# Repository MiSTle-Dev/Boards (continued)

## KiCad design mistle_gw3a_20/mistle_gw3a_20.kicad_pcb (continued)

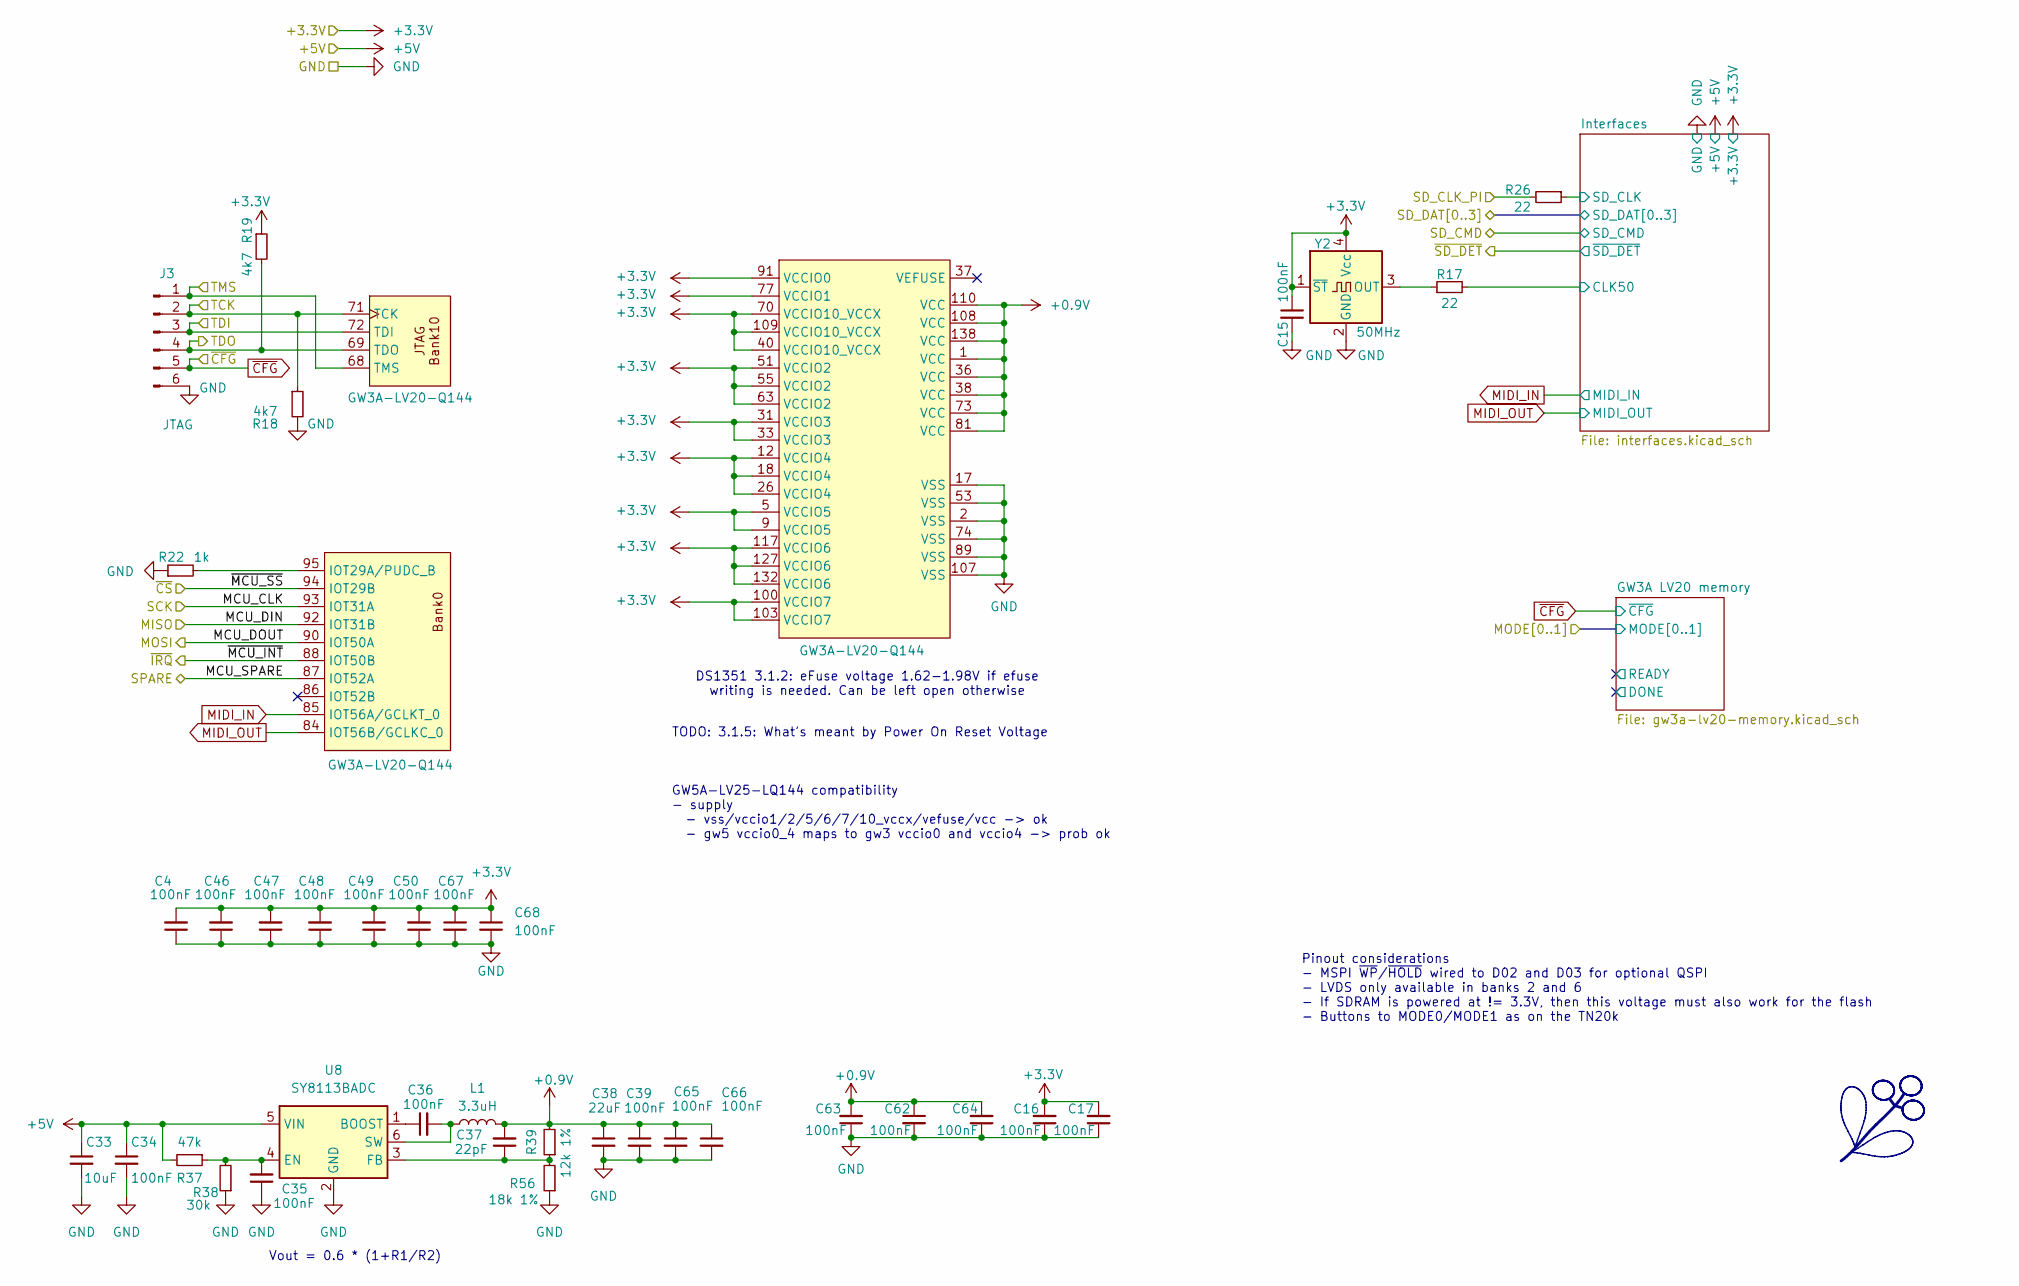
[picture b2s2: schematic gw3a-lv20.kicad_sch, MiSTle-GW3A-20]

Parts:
C4, C15, C16, C17, C35, C36, C46, C47, C48, C49, C50, C62, C63, C64, C65, C66, C67, C68: 100nF; C_0402_1005Metric; LCSC Part # C1525
C33: 10uF; C_0603_1608Metric; LCSC Part # C19702
C34, C39: 100nF; C_0603_1608Metric; LCSC Part # C14663
C37: 22pF; C_0402_1005Metric; LCSC Part # C1555
C38: 22uF; C_0603_1608Metric; LCSC Part # C84419
J3: JTAG; PinHeader_1x06_P2.54mm_Vertical
L1: 3.3uH; L_Sunlord_MWSA0402S; LCSC Part # C408336
R17, R26: 22; R_0402_1005Metric; LCSC Part # C25092
R18, R19: 4k7; R_0402_1005Metric; LCSC Part # C25900
R22: 1k; R_0402_1005Metric; LCSC Part # C11702
R37: 47k; R_0402_1005Metric; LCSC Part # C25792
R38: 30k; R_0402_1005Metric; LCSC Part # C138008
R39: 12k 1%; R_0402_1005Metric; LCSC Part # C25752
R56: 18k 1%; R_0402_1005Metric; LCSC Part # C138044
U7: GW3A-LV20-Q144; LQFP-144_20x20mm_P0.5mm
U8: SY8113BADC; TSOT-23-6; LCSC Part # C78989
Y2: 50MHz; Crystal_SMD_3225-4Pin_3.2x2.5mm; LCSC Part # C2901592

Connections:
+0.9V: C37.2, C38.1, C39.1, C62.1, C63.2, C64.2, C65.1, C66.1, L1.2, R39.2, U7.1 (VCC), U7.36 (VCC), U7.38 (VCC), U7.73 (VCC), U7.81 (VCC), U7.108 (VCC), U7.110 (VCC), U7.138 (VCC)
+3.3V: C4.2, C15.1, C16.2, C17.2, C46.2, C47.2, C48.2, C49.2, C50.2, C67.1, C68.1, R19.1, U7.5 (VCCIO5), U7.9 (VCCIO5), U7.12 (VCCIO4), U7.18 (VCCIO4), U7.26 (VCCIO4), U7.31 (VCCIO3), U7.33 (VCCIO3), U7.40 (VCCIO10_VCCX), U7.51 (VCCIO2), U7.55 (VCCIO2), U7.63 (VCCIO2), U7.70 (VCCIO10_VCCX), U7.77 (VCCIO1), U7.91 (VCCIO0), U7.100 (VCCIO7), U7.103 (VCCIO7), U7.109 (VCCIO10_VCCX), U7.117 (VCCIO6), U7.127 (VCCIO6), U7.132 (VCCIO6), Y2.1 (~ST), Y2.4 (Vcc); also elsewhere on the board
+5V: C33.1, C34.1, R37.2, U8.5 (VIN); also elsewhere on the board
/GW3A-LV20 FPGA/Interfaces/CLK50: R17.2; also elsewhere on the board
/GW3A-LV20 FPGA/Interfaces/SD_CLK: R26.1; also elsewhere on the board
GND: C4.1, C15.2, C16.1, C17.1, C33.2, C34.2, C35.1, C38.2, C39.2, C46.1, C47.1, C48.1, C49.1, C50.1, C62.2, C63.1, C64.1, C65.2, C66.2, C67.2, C68.2, J3.6, R18.2, R22.1, R38.1, R56.1, U7.2 (VSS), U7.17 (VSS), U7.53 (VSS), U7.74 (VSS), U7.89 (VSS), U7.107 (VSS), U8.2 (GND), Y2.2 (GND); also elsewhere on the board
MIDI_IN: U7.85 (IOT56A/GCLKT_0); also elsewhere on the board
MIDI_OUT: U7.84 (IOT56B/GCLKC_0); also elsewhere on the board
MISO: U7.92 (IOT31B); also elsewhere on the board
MOSI: U7.90 (IOT50A); also elsewhere on the board
unnamed: R22.2, U7.95 (IOT29A/PUDC_B)
unnamed: C36.1, U8.1 (BOOST)
unnamed: C35.2, R37.1, R38.2, U8.4 (EN)
unnamed: C37.1, R39.1, R56.2, U8.3 (FB)
unnamed: C36.2, L1.1, U8.6 (SW)
unnamed: R17.1, Y2.3 (OUT)
SCK: U7.93 (IOT31A); also elsewhere on the board
SD_CLK_PI: R26.2; also elsewhere on the board
SPARE: U7.87 (IOT52A); also elsewhere on the board
TCK: J3.2, R18.1, U7.71 (TCK); also elsewhere on the board
TDI: J3.3, U7.72 (TDI); also elsewhere on the board
TDO: J3.4, R19.2, U7.69 (TDO); also elsewhere on the board
TMS: J3.1, U7.68 (TMS); also elsewhere on the board
~CFG: J3.5; also elsewhere on the board
~CS: U7.94 (IOT29B); also elsewhere on the board
~IRQ: U7.88 (IOT50B); also elsewhere on the board

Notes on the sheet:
Vout = 0.6 * (1+R1/R2)
GW5A-LV25-LQ144 compatibility - supply - vss/vccio1/2/5/6/7/10_vccx/vefuse/vcc -> ok - gw5 vccio0_4 maps to gw3 vccio0 and vccio4 -> prob ok
Pinout considerations - MSPI ~{WP}/~{HOLD} wired to D02 and D03 for optional QSPI - LVDS only available in banks 2 and 6 - If SDRAM is powered at != 3.3V, then this voltage must also work for the flash - Buttons to MODE0/MODE1 as on the TN20k
TODO: 3.1.5: What's meant by Power On Reset Voltage
DS1351 3.1.2: eFuse voltage 1.62-1.98V if efuse writing is needed. Can be left open otherwise

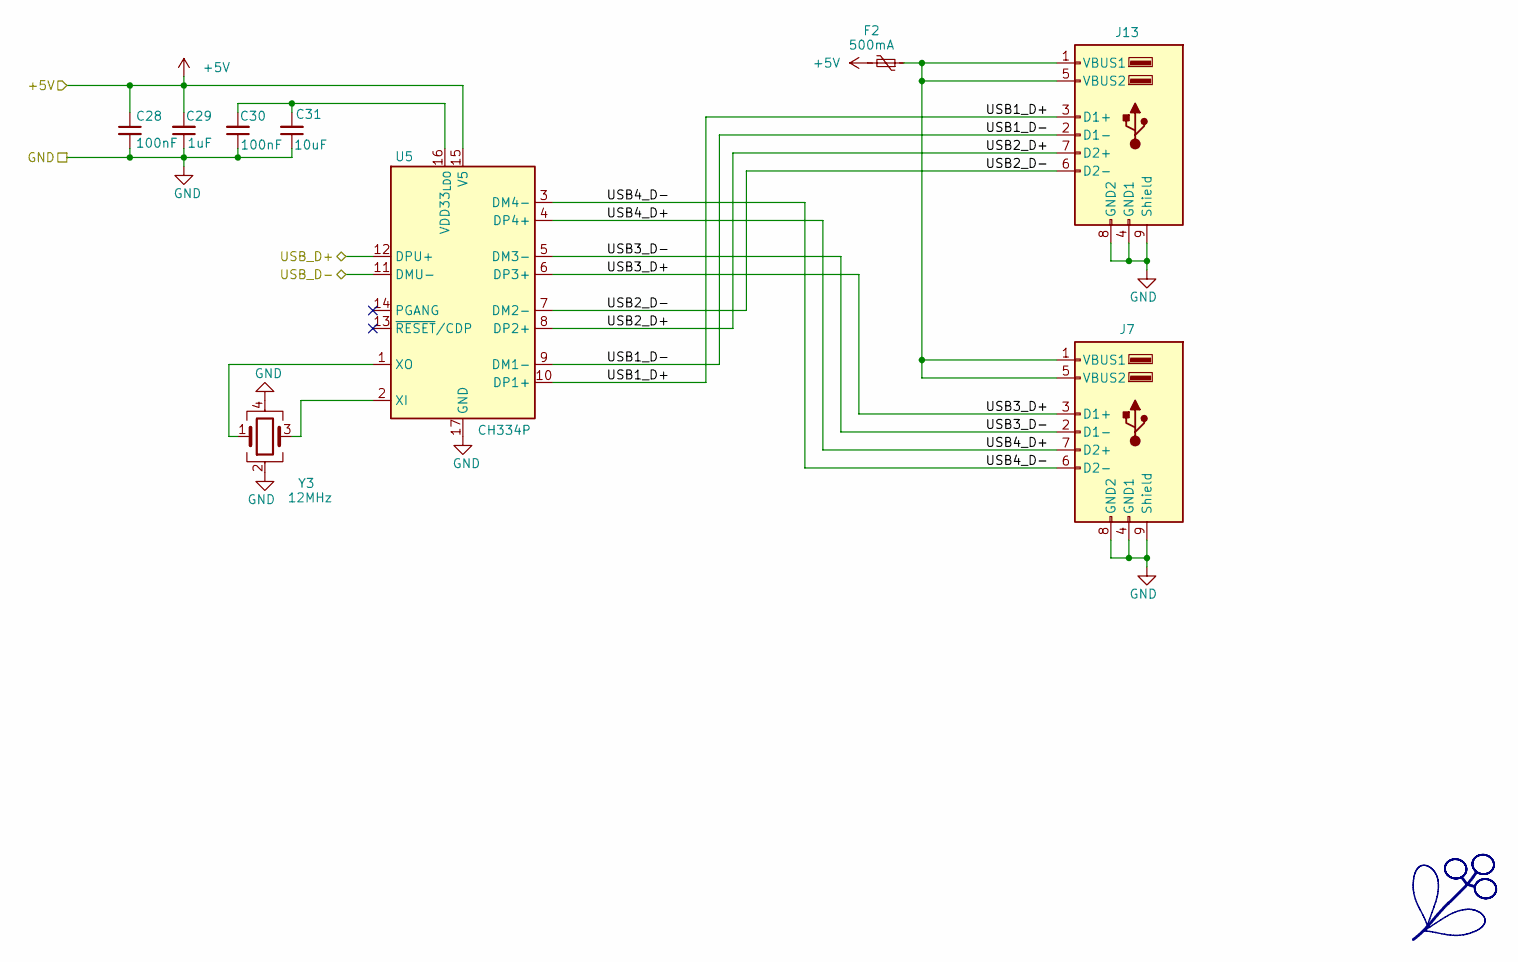
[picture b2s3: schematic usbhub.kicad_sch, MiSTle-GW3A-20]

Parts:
C28, C30: 100nF; C_0402_1005Metric; LCSC Part # C1525
C29: 1uF; C_0402_1005Metric; LCSC Part # C52923
C31: 10uF; C_0402_1005Metric; LCSC Part # C15525
F2: 500mA; Fuse_1206_3216Metric; LCSC Part # C70076
J7, J13: USB_A_Stacked; USB_A_Wuerth_61400826021_Horizontal_Stacked; LCSC Part # C456021
U5: CH334P; QFN-16-1EP_3x3mm_P0.5mm_EP1.45x1.45mm_ThermalVias; LCSC Part # C5373042
Y3: 12MHz; Crystal_SMD_3225-4Pin_3.2x2.5mm; LCSC Part # C9002

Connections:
+5V: C28.1, C29.2, F2.2, U5.15 (V5); also elsewhere on the board
/USB Hub/USB1_D+: J13.3 (D1+), U5.10 (DP1+)
/USB Hub/USB1_D-: J13.2 (D1-), U5.9 (DM1-)
/USB Hub/USB2_D+: J13.7 (D2+), U5.8 (DP2+)
/USB Hub/USB2_D-: J13.6 (D2-), U5.7 (DM2-)
/USB Hub/USB3_D+: J7.3 (D1+), U5.6 (DP3+)
/USB Hub/USB3_D-: J7.2 (D1-), U5.5 (DM3-)
/USB Hub/USB4_D+: J7.7 (D2+), U5.4 (DP4+)
/USB Hub/USB4_D-: J7.6 (D2-), U5.3 (DM4-)
GND: C28.2, C29.1, C30.1, C31.1, J7.4 (GND1), J7.8 (GND2), J7.9 (Shield), J13.4 (GND1), J13.8 (GND2), J13.9 (Shield), U5.17 (GND), Y3.2, Y3.4; also elsewhere on the board
unnamed: F2.1, J7.1 (VBUS1), J7.5 (VBUS2), J13.1 (VBUS1), J13.5 (VBUS2)
unnamed: C30.2, C31.2, U5.16 (VDD33_{LDO})
unnamed: U5.2 (XI), Y3.3
unnamed: U5.1 (XO), Y3.1
USB D+: U5.12 (DPU+); also elsewhere on the board
USB D-: U5.11 (DMU-); also elsewhere on the board

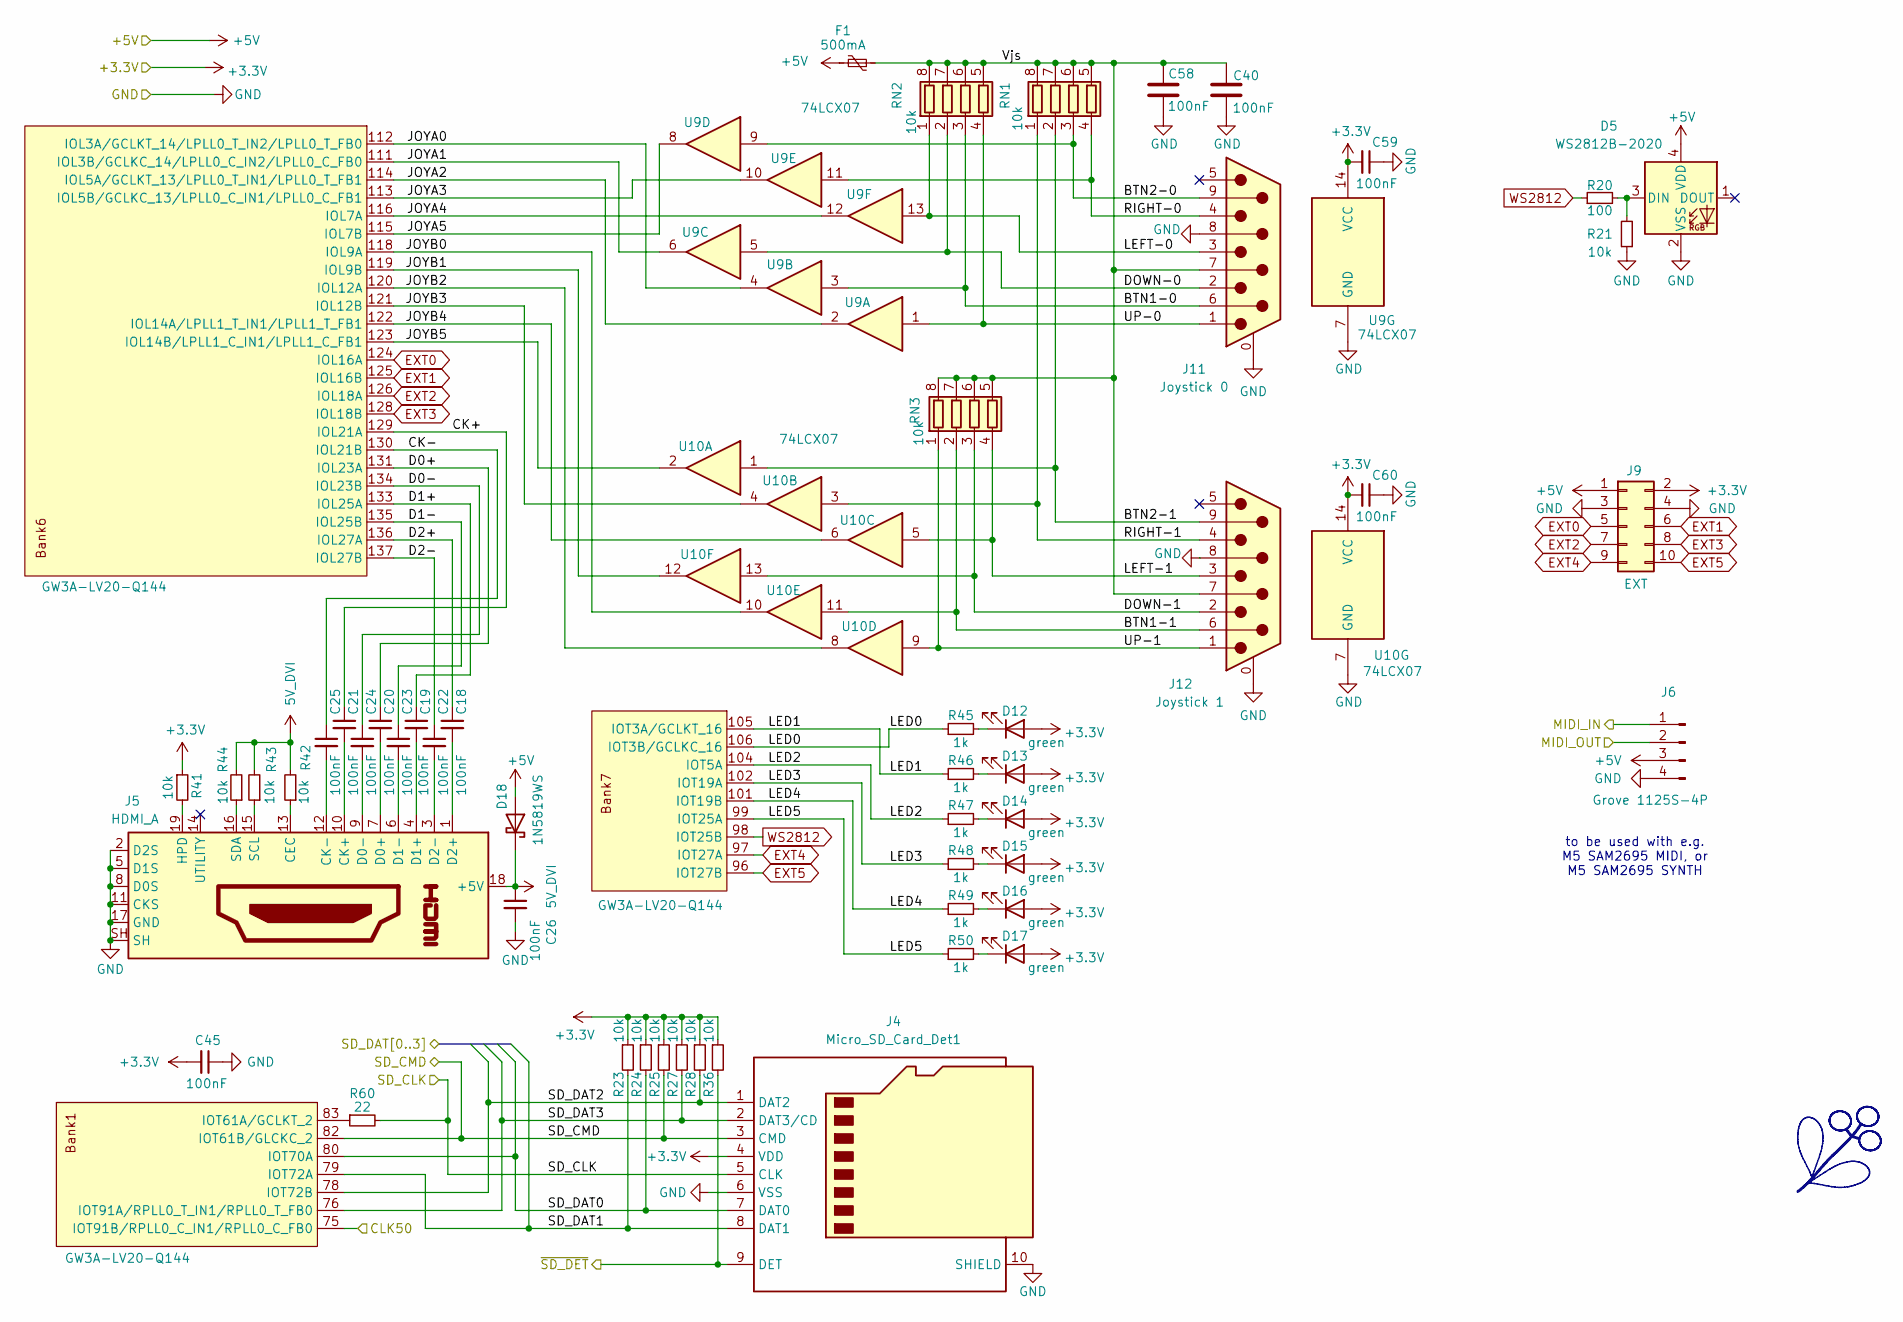
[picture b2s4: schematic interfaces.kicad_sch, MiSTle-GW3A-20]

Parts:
C18, C19, C20, C21, C22, C23, C24, C25, C26, C40, C45, C58, C59, C60: 100nF; C_0402_1005Metric; LCSC Part # C1525
D5: WS2812B-2020; LED_WS2812B-2020_PLCC4_2.0x2.0mm; LCSC Part # C965555
D12, D13, D14, D15, D16, D17: green; LED_0805_2012Metric; LCSC Part # C2297
D18: 1N5819WS; D_SOD-323; LCSC Part # C191023
F1: 500mA; Fuse_1206_3216Metric; LCSC Part # C70076
J4: Micro_SD_Card_Det1; TF-015; LCSC Part # C393941
J5: HDMI_A; HDMI_A_Molex_208658-1001_Horizontal; LCSC Part # C720616
J6: Grove 1125S-4P; NS-Tech_Grove_1x04_P2mm_Vertical
J9: EXT; IDC-Header_2x05_P2.54mm_Vertical; LCSC Part # C271747
J11: Joystick 0; DSUB-9_Pins_Horizontal_P2.77x2.84mm_EdgePinOffset7.70mm_Hou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; LCSC Part # C141880
J12: Joystick 1; DSUB-9_Pins_Horizontal_P2.77x2.84mm_EdgePinOffset7.70mm_Hou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; LCSC Part # C141880
R20: 100; R_0402_1005Metric; LCSC Part # C25076
R21, R23, R24, R25, R27, R28, R36, R41, R42, R43, R44: 10k; R_0402_1005Metric; LCSC Part # C25744
R45, R46, R47, R48, R49, R50: 1k; R_0402_1005Metric; LCSC Part # C11702
R60: 22; R_0402_1005Metric; LCSC Part # C25092
RN1, RN2, RN3: 10k; R_Array_Concave_4x0603; LCSC Part # C110924
U7: GW3A-LV20-Q144; LQFP-144_20x20mm_P0.5mm
U9, U10: 74LCX07; TSSOP-14_4.4x5mm_P0.65mm; LCSC Part # C2676034

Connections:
5V_DVI: C26.1, D18.1 (K), J5.18 (+5V), R42.2, R43.2, R44.2
+3.3V: C45.2, C59.2, C60.2, D12.2 (A), D13.2 (A), D14.2 (A), D15.2 (A), D16.2 (A), D17.2 (A), J4.4 (VDD), J9.2, R23.1, R24.1, R25.1, R27.1, R28.1, R36.1, R41.1, U9.14 (VCC), U10.14 (VCC); also elsewhere on the board
+5V: D5.4 (VDD), D18.2 (A), F1.2, J6.3, J9.1; also elsewhere on the board
/GW3A-LV20 FPGA/Interfaces/BTN1-0: J11.6, RN2.3 (R3.1), U9.3
/GW3A-LV20 FPGA/Interfaces/BTN1-1: J12.6, RN3.2 (R2.1), U10.11
/GW3A-LV20 FPGA/Interfaces/BTN2-0: J11.9, RN1.3 (R3.1), U9.9
/GW3A-LV20 FPGA/Interfaces/BTN2-1: J12.9, RN1.2 (R2.1), U10.1
/GW3A-LV20 FPGA/Interfaces/CK+: C21.1, U7.129 (IOL21A)
/GW3A-LV20 FPGA/Interfaces/CK-: C25.1, U7.130 (IOL21B)
/GW3A-LV20 FPGA/Interfaces/CLK50: U7.75 (IOT91B/RPLL0_C_IN1/RPLL0_C_FB0); also elsewhere on the board
/GW3A-LV20 FPGA/Interfaces/D0+: C20.1, U7.131 (IOL23A)
/GW3A-LV20 FPGA/Interfaces/D0-: C24.1, U7.134 (IOL23B)
/GW3A-LV20 FPGA/Interfaces/D1+: C19.1, U7.133 (IOL25A)
/GW3A-LV20 FPGA/Interfaces/D1-: C23.1, U7.135 (IOL25B)
/GW3A-LV20 FPGA/Interfaces/D2+: C18.1, U7.136 (IOL27A)
/GW3A-LV20 FPGA/Interfaces/D2-: C22.1, U7.137 (IOL27B)
/GW3A-LV20 FPGA/Interfaces/DOWN-0: J11.2, RN2.2 (R2.1), U9.5
/GW3A-LV20 FPGA/Interfaces/DOWN-1: J12.2, RN3.3 (R3.1), U10.13
/GW3A-LV20 FPGA/Interfaces/JOYA0: U7.112 (IOL3A/GCLKT_14/LPLL0_T_IN2/LPLL0_T_FB0), U9.4
/GW3A-LV20 FPGA/Interfaces/JOYA1: U7.111 (IOL3B/GCLKC_14/LPLL0_C_IN2/LPLL0_C_FB0), U9.6
/GW3A-LV20 FPGA/Interfaces/JOYA2: U7.114 (IOL5A/GCLKT_13/LPLL0_T_IN1/LPLL0_T_FB1), U9.2
/GW3A-LV20 FPGA/Interfaces/JOYA3: U7.113 (IOL5B/GCLKC_13/LPLL0_C_IN1/LPLL0_C_FB1), U9.10
/GW3A-LV20 FPGA/Interfaces/JOYA4: U7.116 (IOL7A), U9.12
/GW3A-LV20 FPGA/Interfaces/JOYA5: U7.115 (IOL7B), U9.8
/GW3A-LV20 FPGA/Interfaces/JOYB0: U7.118 (IOL9A), U10.10
/GW3A-LV20 FPGA/Interfaces/JOYB1: U7.119 (IOL9B), U10.12
/GW3A-LV20 FPGA/Interfaces/JOYB2: U7.120 (IOL12A), U10.8
/GW3A-LV20 FPGA/Interfaces/JOYB3: U7.121 (IOL12B), U10.4
/GW3A-LV20 FPGA/Interfaces/JOYB4: U7.122 (IOL14A/LPLL1_T_IN1/LPLL1_T_FB1), U10.6
/GW3A-LV20 FPGA/Interfaces/JOYB5: U7.123 (IOL14B/LPLL1_C_IN1/LPLL1_C_FB1), U10.2
/GW3A-LV20 FPGA/Interfaces/LED0: R45.1, U7.106 (IOT3B/GCLKC_16)
/GW3A-LV20 FPGA/Interfaces/LED1: R46.1, U7.105 (IOT3A/GCLKT_16)
/GW3A-LV20 FPGA/Interfaces/LED2: R47.1, U7.104 (IOT5A)
/GW3A-LV20 FPGA/Interfaces/LED3: R48.1, U7.102 (IOT19A)
/GW3A-LV20 FPGA/Interfaces/LED4: R49.1, U7.101 (IOT19B)
/GW3A-LV20 FPGA/Interfaces/LED5: R50.1, U7.99 (IOT25A)
/GW3A-LV20 FPGA/Interfaces/LEFT-0: J11.3, RN2.1 (R1.1), U9.13
/GW3A-LV20 FPGA/Interfaces/LEFT-1: J12.3, RN3.4 (R4.1), U10.5
/GW3A-LV20 FPGA/Interfaces/RIGHT-0: J11.4, RN1.4 (R4.1), U9.11
/GW3A-LV20 FPGA/Interfaces/RIGHT-1: J12.4, RN1.1 (R1.1), U10.3
/GW3A-LV20 FPGA/Interfaces/SD_CLK: J4.5 (CLK), R60.2; also elsewhere on the board
/GW3A-LV20 FPGA/Interfaces/UP-0: J11.1, RN2.4 (R4.1), U9.1
/GW3A-LV20 FPGA/Interfaces/UP-1: J12.1, RN3.1 (R1.1), U10.9
/GW3A-LV20 FPGA/Interfaces/Vjs: C40.2, C58.2, F1.1, J11.7, J12.7, RN1.5 (R4.2), RN1.6 (R3.2), RN1.7 (R2.2), RN1.8 (R1.2), RN2.5 (R4.2), RN2.6 (R3.2), RN2.7 (R2.2), RN2.8 (R1.2), RN3.5 (R4.2), RN3.6 (R3.2), RN3.7 (R2.2), RN3.8 (R1.2)
EXT0: J9.5, U7.124 (IOL16A)
EXT1: J9.6, U7.125 (IOL16B)
EXT2: J9.7, U7.126 (IOL18A)
EXT3: J9.8, U7.128 (IOL18B)
EXT4: J9.9, U7.97 (IOT27A)
EXT5: J9.10, U7.96 (IOT27B)
GND: C26.2, C40.1, C45.1, C58.1, C59.1, C60.1, D5.2 (VSS), J4.6 (VSS), J4.10 (SHIELD), J5.2 (D2S), J5.5 (D1S), J5.8 (D0S), J5.11 (CKS), J5.17 (GND), J5.SH, J6.4, J9.3, J9.4, J11.0 (PAD), J11.8, J12.0 (PAD), J12.8, R21.1, U9.7 (GND), U10.7 (GND); also elsewhere on the board
MIDI_IN: J6.1; also elsewhere on the board
MIDI_OUT: J6.2; also elsewhere on the board
unnamed: D5.3 (DIN), R20.2, R21.2
unnamed: D12.1 (K), R45.2
unnamed: D13.1 (K), R46.2
unnamed: D14.1 (K), R47.2
unnamed: D15.1 (K), R48.2
unnamed: D16.1 (K), R49.2
unnamed: D17.1 (K), R50.2
unnamed: J5.13 (CEC), R42.1
unnamed: C21.2, J5.10 (CK+)
unnamed: C25.2, J5.12 (CK-)
unnamed: C20.2, J5.7 (D0+)
unnamed: C24.2, J5.9 (D0-)
unnamed: C19.2, J5.4 (D1+)
unnamed: C23.2, J5.6 (D1-)
unnamed: C18.2, J5.1 (D2+)
unnamed: C22.2, J5.3 (D2-)
unnamed: J5.19 (HPD), R41.2
unnamed: J5.15 (SCL), R43.1
unnamed: J5.16 (SDA), R44.1
unnamed: R60.1, U7.83 (IOT61A/GCLKT_2)
SD_CMD: J4.3 (CMD), R25.2, U7.82 (IOT61B/GLCKC_2); also elsewhere on the board
SD_DAT0: J4.7 (DAT0), R24.2, U7.80 (IOT70A); also elsewhere on the board
SD_DAT1: J4.8 (DAT1), R23.2, U7.79 (IOT72A)
SD_DAT2: J4.1 (DAT2), R28.2, U7.78 (IOT72B)
SD_DAT3: J4.2 (DAT3/CD), R27.2, U7.76 (IOT91A/RPLL0_T_IN1/RPLL0_T_FB0); also elsewhere on the board
WS2812: R20.1, U7.98 (IOT25B)
~SD_DET: J4.9 (DET), R36.2; also elsewhere on the board

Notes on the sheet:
to be used with e.g. M5 SAM2695 MIDI, or M5 SAM2695 SYNTH

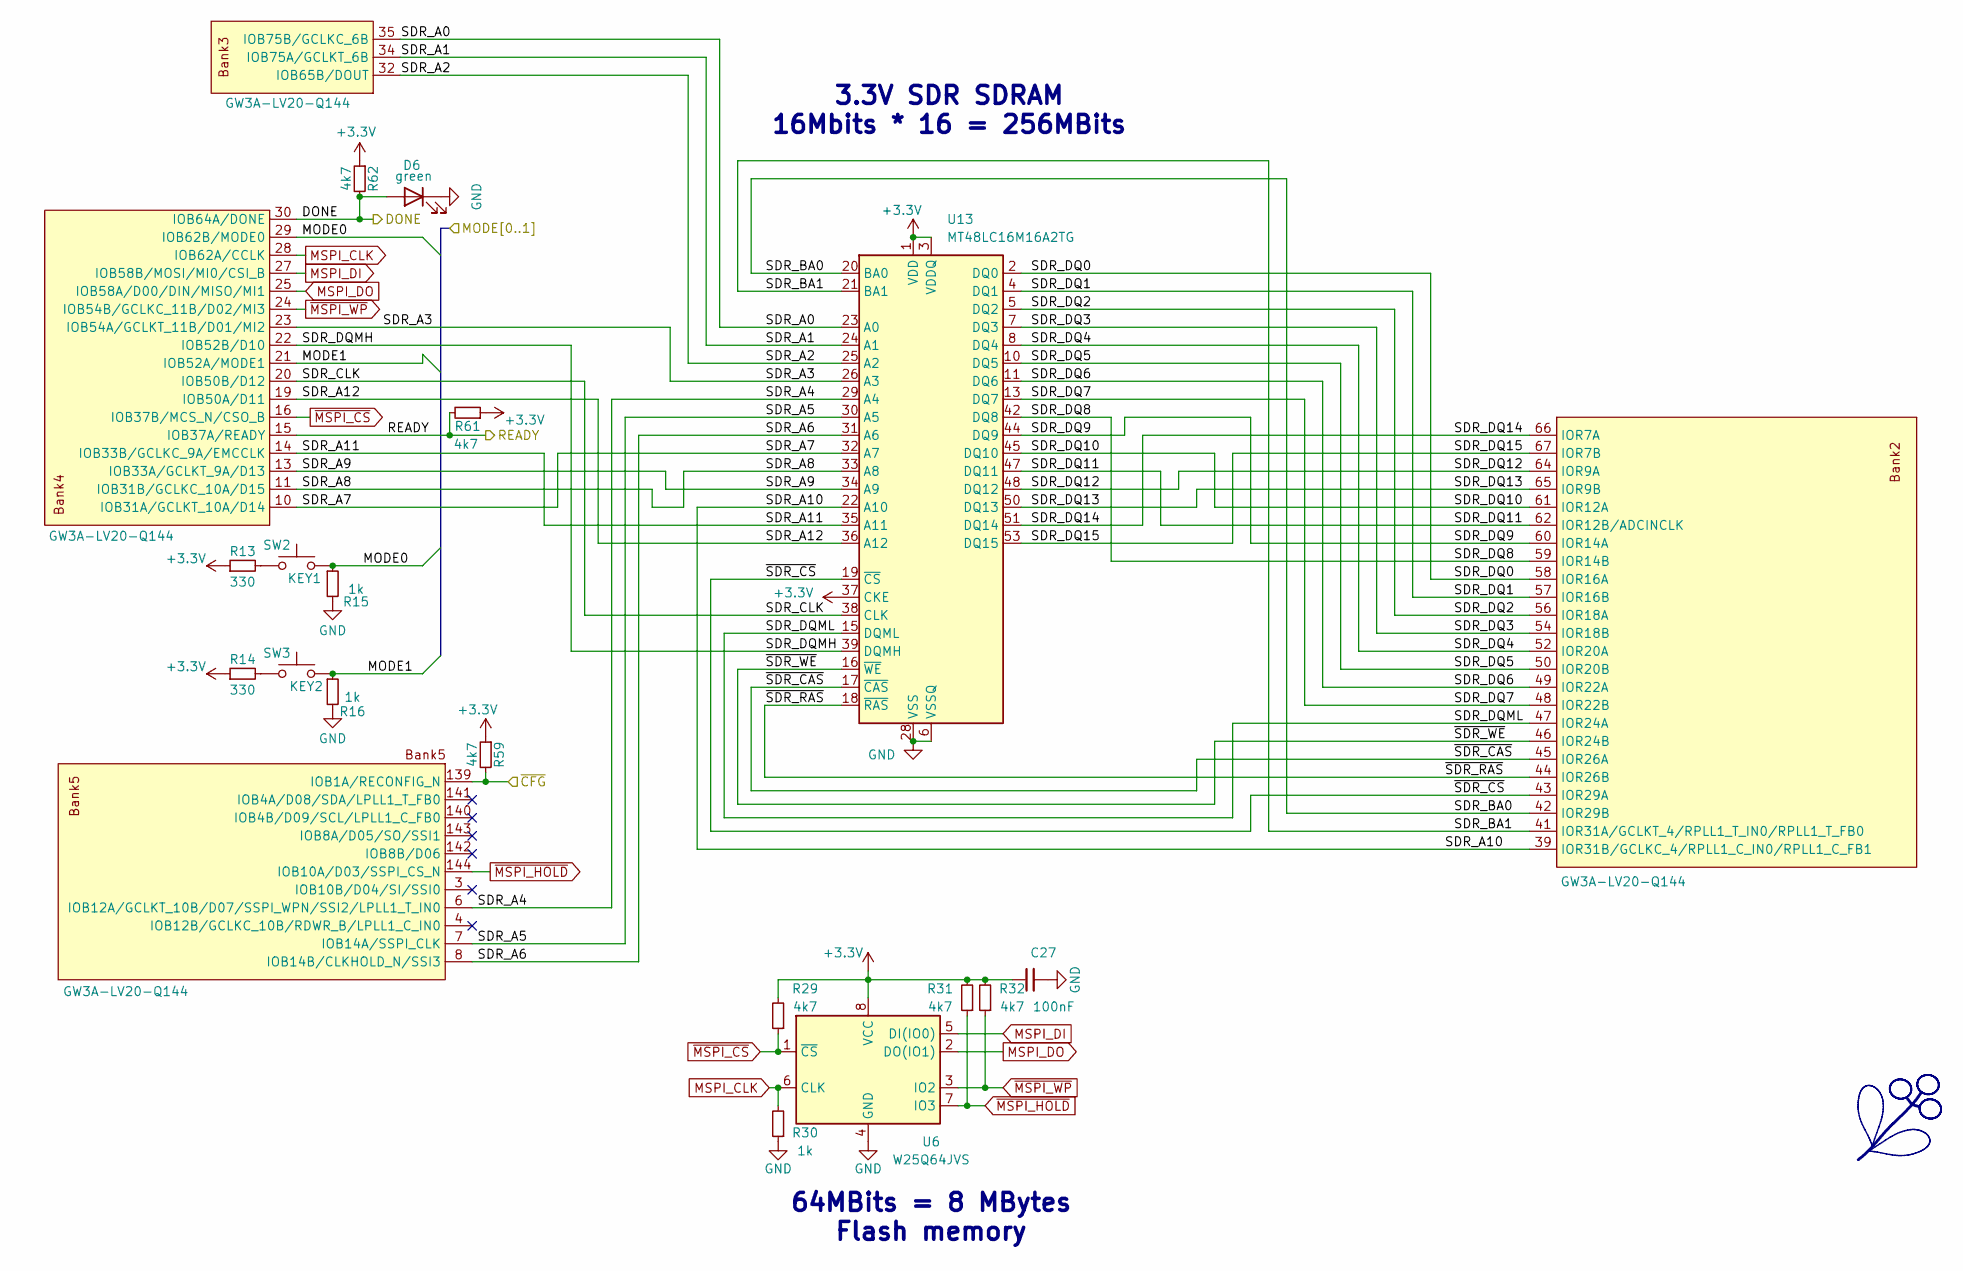
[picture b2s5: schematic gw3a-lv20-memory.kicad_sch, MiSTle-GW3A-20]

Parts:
C27: 100nF; C_0402_1005Metric; LCSC Part # C1525
D6: green; LED_0805_2012Metric; LCSC Part # C2297
R13, R14: 330; R_0402_1005Metric; LCSC Part # C105875
R15, R16, R30: 1k; R_0402_1005Metric; LCSC Part # C11702
R29, R31, R32, R59, R61, R62: 4k7; R_0402_1005Metric; LCSC Part # C25900
SW2: KEY1; SW_SPST_TL3342; LCSC Part # C318884
SW3: KEY2; SW_SPST_TL3342; LCSC Part # C318884
U6: W25Q64JVS; SOIC-8_5.3x5.3mm_P1.27mm; LCSC Part # C179171
U7: GW3A-LV20-Q144; LQFP-144_20x20mm_P0.5mm
U13: MT48LC16M16A2TG; TSOP-II-54_22.2x10.16mm_P0.8mm; LCSC Part # C62246

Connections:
+3.3V: C27.1, R13.1, R14.1, R29.2, R31.2, R32.2, R59.1, R61.1, R62.1, U6.8 (VCC), U13.1 (VDD), U13.3 (VDDQ), U13.9 (VDDQ), U13.14 (VDD), U13.27 (VDD), U13.37 (CKE), U13.43 (VDDQ), U13.49 (VDDQ); also elsewhere on the board
/GW3A-LV20 FPGA/GW3A LV20 memory/DONE: D6.2 (A), R62.2, U7.30 (IOB64A/DONE)
/GW3A-LV20 FPGA/GW3A LV20 memory/READY: R61.2, U7.15 (IOB37A/READY)
/GW3A-LV20 FPGA/GW3A LV20 memory/SDR_A0: U7.35 (IOB75B/GCLKC_6B), U13.23 (A0)
/GW3A-LV20 FPGA/GW3A LV20 memory/SDR_A1: U7.34 (IOB75A/GCLKT_6B), U13.24 (A1)
/GW3A-LV20 FPGA/GW3A LV20 memory/SDR_A2: U7.32 (IOB65B/DOUT), U13.25 (A2)
/GW3A-LV20 FPGA/GW3A LV20 memory/SDR_A3: U7.23 (IOB54A/GCLKT_11B/D01/MI2), U13.26 (A3)
/GW3A-LV20 FPGA/GW3A LV20 memory/SDR_A4: U7.6 (IOB12A/GCLKT_10B/D07/SSPI_WPN/SSI2/LPLL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), U13.29 (A4)
/GW3A-LV20 FPGA/GW3A LV20 memory/SDR_A5: U7.7 (IOB14A/SSPI_CLK), U13.30 (A5)
/GW3A-LV20 FPGA/GW3A LV20 memory/SDR_A6: U7.8 (IOB14B/CLKHOLD_N/SSI3), U13.31 (A6)
/GW3A-LV20 FPGA/GW3A LV20 memory/SDR_A7: U7.10 (IOB31A/GCLKT_10A/D14), U13.32 (A7)
/GW3A-LV20 FPGA/GW3A LV20 memory/SDR_A8: U7.11 (IOB31B/GCLKC_10A/D15), U13.33 (A8)
/GW3A-LV20 FPGA/GW3A LV20 memory/SDR_A9: U7.13 (IOB33A/GCLKT_9A/D13), U13.34 (A9)
/GW3A-LV20 FPGA/GW3A LV20 memory/SDR_A10: U7.39 (IOR31B/GCLKC_4/RPLL1_C_IN0/RPLL1_C_FB1), U13.22 (A10)
/GW3A-LV20 FPGA/GW3A LV20 memory/SDR_A11: U7.14 (IOB33B/GCLKC_9A/EMCCLK), U13.35 (A11)
/GW3A-LV20 FPGA/GW3A LV20 memory/SDR_A12: U7.19 (IOB50A/D11), U13.36 (A12)
/GW3A-LV20 FPGA/GW3A LV20 memory/SDR_BA0: U7.42 (IOR29B), U13.20 (BA0)
/GW3A-LV20 FPGA/GW3A LV20 memory/SDR_BA1: U7.41 (IOR31A/GCLKT_4/RPLL1_T_IN0/RPLL1_T_FB0), U13.21 (BA1)
/GW3A-LV20 FPGA/GW3A LV20 memory/SDR_CLK: U7.20 (IOB50B/D12), U13.38 (CLK)
/GW3A-LV20 FPGA/GW3A LV20 memory/SDR_DQ0: U7.58 (IOR16A), U13.2 (DQ0)
/GW3A-LV20 FPGA/GW3A LV20 memory/SDR_DQ1: U7.57 (IOR16B), U13.4 (DQ1)
/GW3A-LV20 FPGA/GW3A LV20 memory/SDR_DQ2: U7.56 (IOR18A), U13.5 (DQ2)
/GW3A-LV20 FPGA/GW3A LV20 memory/SDR_DQ3: U7.54 (IOR18B), U13.7 (DQ3)
/GW3A-LV20 FPGA/GW3A LV20 memory/SDR_DQ4: U7.52 (IOR20A), U13.8 (DQ4)
/GW3A-LV20 FPGA/GW3A LV20 memory/SDR_DQ5: U7.50 (IOR20B), U13.10 (DQ5)
/GW3A-LV20 FPGA/GW3A LV20 memory/SDR_DQ6: U7.49 (IOR22A), U13.11 (DQ6)
/GW3A-LV20 FPGA/GW3A LV20 memory/SDR_DQ7: U7.48 (IOR22B), U13.13 (DQ7)
/GW3A-LV20 FPGA/GW3A LV20 memory/SDR_DQ8: U7.59 (IOR14B), U13.42 (DQ8)
/GW3A-LV20 FPGA/GW3A LV20 memory/SDR_DQ9: U7.60 (IOR14A), U13.44 (DQ9)
/GW3A-LV20 FPGA/GW3A LV20 memory/SDR_DQ10: U7.61 (IOR12A), U13.45 (DQ10)
/GW3A-LV20 FPGA/GW3A LV20 memory/SDR_DQ11: U7.62 (IOR12B/ADCINCLK), U13.47 (DQ11)
/GW3A-LV20 FPGA/GW3A LV20 memory/SDR_DQ12: U7.64 (IOR9A), U13.48 (DQ12)
/GW3A-LV20 FPGA/GW3A LV20 memory/SDR_DQ13: U7.65 (IOR9B), U13.50 (DQ13)
/GW3A-LV20 FPGA/GW3A LV20 memory/SDR_DQ14: U7.66 (IOR7A), U13.51 (DQ14)
/GW3A-LV20 FPGA/GW3A LV20 memory/SDR_DQ15: U7.67 (IOR7B), U13.53 (DQ15)
/GW3A-LV20 FPGA/GW3A LV20 memory/SDR_DQMH: U7.22 (IOB52B/D10), U13.39 (DQMH)
/GW3A-LV20 FPGA/GW3A LV20 memory/SDR_DQML: U7.47 (IOR24A), U13.15 (DQML)
/GW3A-LV20 FPGA/GW3A LV20 memory/~SDR_CAS: U7.45 (IOR26A), U13.17 (~CAS)
/GW3A-LV20 FPGA/GW3A LV20 memory/~SDR_CS: U7.43 (IOR29A), U13.19 (~CS)
/GW3A-LV20 FPGA/GW3A LV20 memory/~SDR_RAS: U7.44 (IOR26B), U13.18 (~RAS)
/GW3A-LV20 FPGA/GW3A LV20 memory/~SDR_WE: U7.46 (IOR24B), U13.16 (~WE)
GND: C27.2, D6.1 (K), R15.2, R16.2, R30.1, U6.4 (GND), U13.6 (VSSQ), U13.12 (VSSQ), U13.28 (VSS), U13.41 (VSS), U13.46 (VSSQ), U13.52 (VSSQ), U13.54 (VSS); also elsewhere on the board
MODE0: R15.1, SW2.2, U7.29 (IOB62B/MODE0); also elsewhere on the board
MODE1: R16.1, SW3.2, U7.21 (IOB52A/MODE1); also elsewhere on the board
MSPI_CLK: R30.2, U6.6 (CLK), U7.28 (IOB62A/CCLK)
MSPI_DI: U6.5 (DI(IO0)), U7.27 (IOB58B/MOSI/MI0/CSI_B)
MSPI_DO: U6.2 (DO(IO1)), U7.25 (IOB58A/D00/DIN/MISO/MI1)
unnamed: R13.2, SW2.1
unnamed: R14.2, SW3.1
~CFG: R59.2, U7.139 (IOB1A/RECONFIG_N); also elsewhere on the board
~MSPI_CS: R29.1, U6.1 (~CS), U7.16 (IOB37B/MCS_N/CSO_B)
~MSPI_HOLD: R31.1, U6.7 (IO3), U7.144 (IOB10A/D03/SSPI_CS_N)
~MSPI_WP: R32.1, U6.3 (IO2), U7.24 (IOB54B/GCLKC_11B/D02/MI3)

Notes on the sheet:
64MBits = 8 MBytes Flash memory
3.3V SDR SDRAM 16Mbits * 16 = 256MBits

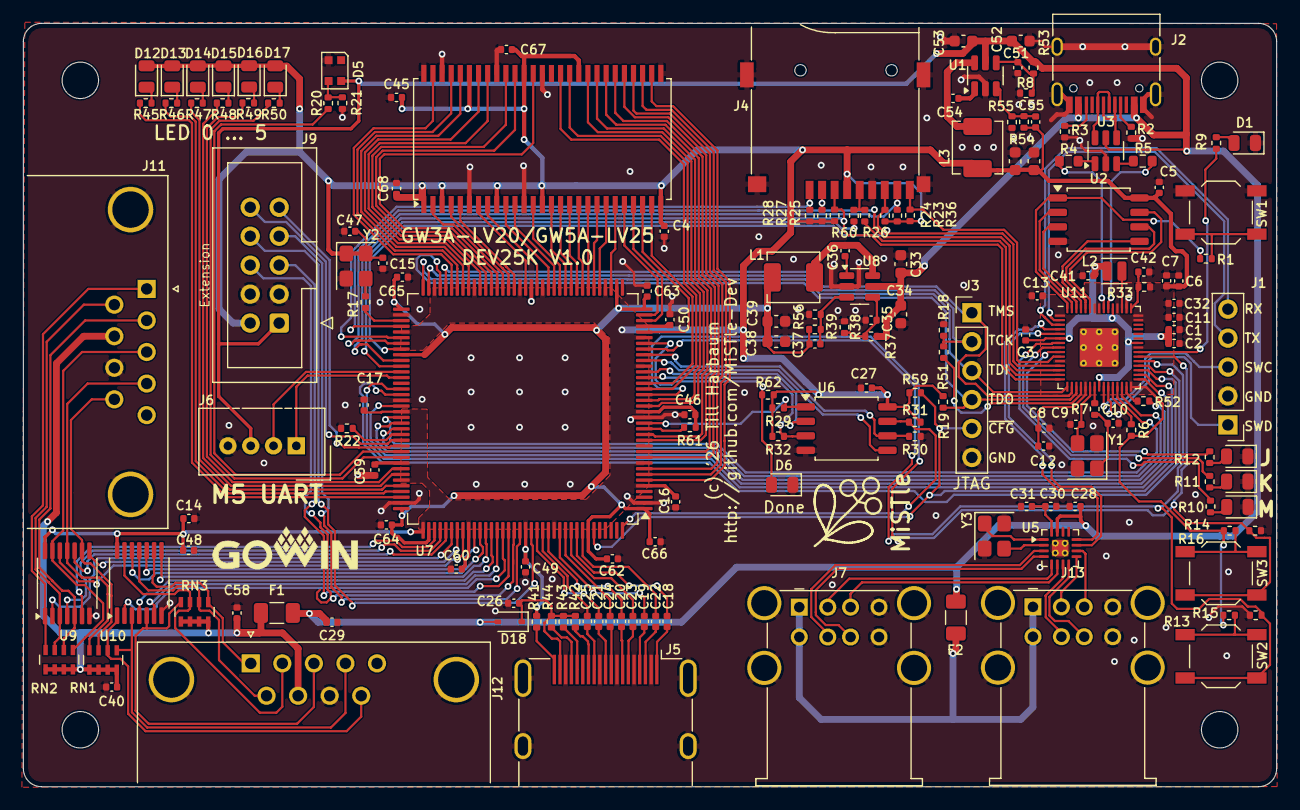
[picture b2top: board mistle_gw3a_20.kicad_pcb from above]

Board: 2 copper layers, 110.0 x 67.0 mm, 175 parts (0 on the bottom side), 203 nets.

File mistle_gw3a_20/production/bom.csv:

Designator,Footprint,Quantity,Value,LCSC Part #
"C1, C29, C6, C8",0402,4,1uF,C52923
"C10, C37, C55, C9",0402,4,22pF,C1555
"C11, C12, C13, C14, C15, C16, C17, C18, C19, C2, C20, C21, C22, C23, C24, C25, C26, C27, C28, C3, C30, C35, C36, C4, C40, C45, C46, C47, C48, C49, C5, C50, C51, C54, C58, C59, C60, C62, C63, C64, C65, C66, C67, C68",0402,44,100nF,C1525
"C31, C7",0402,2,10uF,C15525
"C32, C41, C42",0402,3,4.7u,C23733
"C33, C53",0603,2,10uF,C19702
"C34, C39, C52, C57",0603,4,100nF,C14663
"C38, C56",0603,2,22uF,C84419
"D1, D12, D13, D14, D15, D16, D17, D6",0805,8,green,C2297
D18,D_SOD-323,1,1N5819WS,C191023
D2,0805,1,Mouse,C2297
D3,0805,1,Keyboard,C2297
D4,0805,1,Joystick,C2297
D5,LED_WS2812B-2020_PLCC4_2.0x2.0mm,1,WS2812B-2020,C965555
"F1, F2",1206,2,500mA,C70076
J1,PinHeader_1x05_P2.54mm_Vertical,1,SWD,C492404
J11,DSUB-9_Pins_Horizontal_P2.77x2.84mm_EdgePinOffset7.70mm_Housed_MountingHolesOffset9.12mm,1,Joystick 0,C141880
J12,DSUB-9_Pins_Horizontal_P2.77x2.84mm_EdgePinOffset7.70mm_Housed_MountingHolesOffset9.12mm,1,Joystick 1,C141880
"J13, J7",USB_A_Wuerth_61400826021_Horizontal_Stacked,2,USB_A_Stacked,C456021
J2,USB_C_Receptacle_HRO_TYPE-C-31-M-12,1,USB_C_Receptacle_USB2.0,C165948
J4,TF-015,1,Micro_SD_Card_Det1,C393941
J5,HDMI_A_Molex_208658-1001_Horizontal,1,HDMI_A,C720616
J9,IDC-Header_2x05_P2.54mm_Vertical,1,EXT,C271747
"L1, L3",L_Sunlord_MWSA0402S,2,3.3uH,C408336
L2,L_Changjiang_FTC201610D,1,3.3u,C42411119
"R1, R10, R11, R12, R15, R16, R22, R30, R45, R46, R47, R48, R49, R50, R6, R7, R9",0402,17,1k,C11702
"R13, R14",0402,2,330,C105875
"R17, R26, R51, R52, R60",0402,5,22,C25092
"R18, R19, R29, R31, R32, R59, R61, R62",0402,8,4k7,C25900
"R2, R3",0402,2,5k1,C25905
R20,0402,1,100,C25076
"R21, R23, R24, R25, R27, R28, R36, R41, R42, R43, R44",0402,11,10k,C25744
R33,0402,1,33,C25105
"R37, R53",0402,2,47k,C25792
"R38, R8",0402,2,30k,C138008
R39,0402,1,12k 1%,C25752
"R4, R5",0603,2,27R,C25190
R54,0402,1,15k 1%,C25756
R55,0402,1,3k3 1%,C25890
R56,0402,1,18k 1%,C138044
"RN1, RN2, RN3",R_Array_Concave_4x0603,3,10k,C110924
SW1,SW_SPST_TL3342,1,Boot,C318884
SW2,SW_SPST_TL3342,1,KEY1,C318884
SW3,SW_SPST_TL3342,1,KEY2,C318884
"U1, U8",TSOT-23-6,2,SY8113BADC,C78989
"U10, U9",TSSOP-14_4.4x5mm_P0.65mm,2,74LCX07,C2676034
U11,RP2350-QFN-60-1EP_7x7_P0.4mm_EP3.4x3.4mm_ThermalVias,1,RP2350_60QFN,C42411118
U13,TSOP-II-54_22.2x10.16mm_P0.8mm,1,MT48LC16M16A2TG,C62246
"U2, U6",SOIC-8_5.3x5.3mm_P1.27mm,2,W25Q64JVS,C179171
U3,SOT-23-6,1,USBLC6-2SC6,C2827654
U5,QFN-16-1EP_3x3mm_P0.5mm_EP1.45x1.45mm_ThermalVias,1,CH334P,C5373042
U7,LQFP-144_20x20mm_P0.5mm,1,GW3A-LV20-Q144,
Y1,Crystal_SMD_3225-4Pin_3.2x2.5mm,1,12MHz,C20625731
Y2,Crystal_SMD_3225-4Pin_3.2x2.5mm,1,50MHz,C2901592
Y3,Crystal_SMD_3225-4Pin_3.2x2.5mm,1,12MHz,C9002
